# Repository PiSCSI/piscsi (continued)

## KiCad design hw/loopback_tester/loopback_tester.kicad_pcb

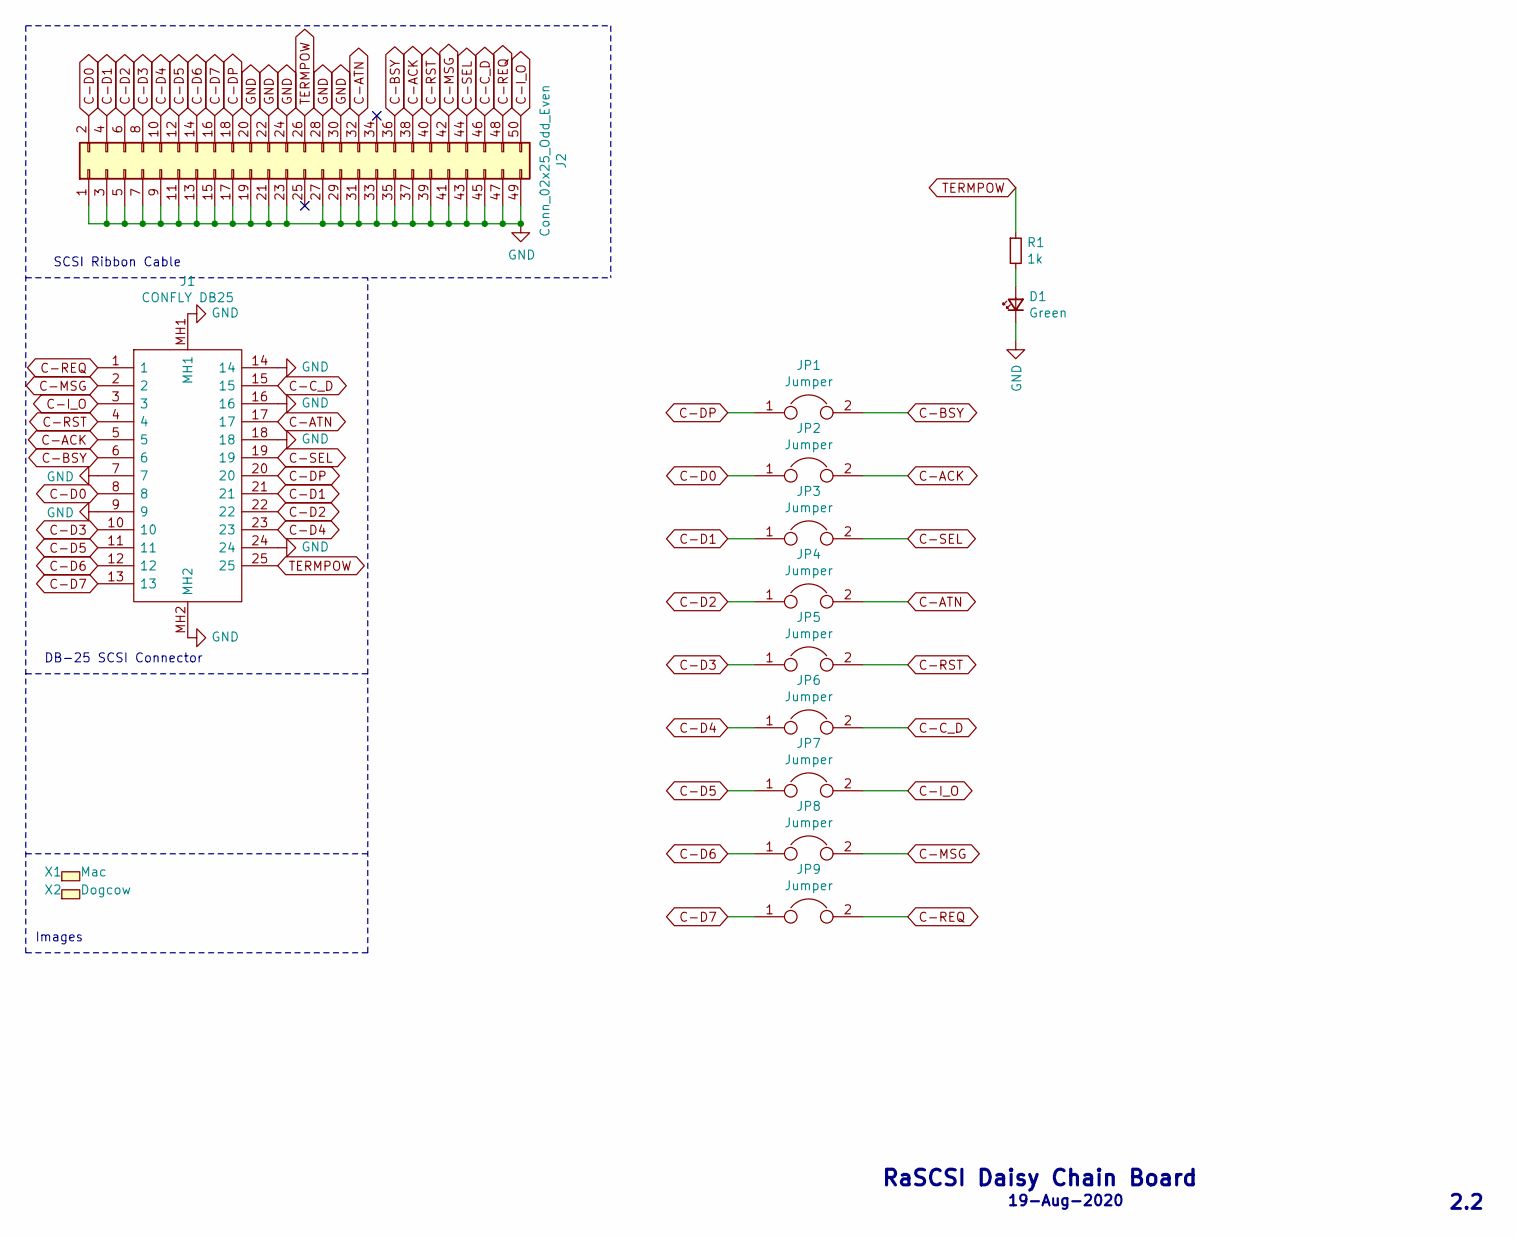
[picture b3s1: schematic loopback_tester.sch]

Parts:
D1: Green; LED_0805_2012Metric; LCSC C2297
J1: CONFLY DB25; L717SDB25PA4CH4F; Mouser Part Number 523-L717SDB25PA4CH4F
J2: Conn_02x25_Odd_Even; PinSocket_2x25_P2.54mm_Vertical; LCSC C40024
JP1, JP2, JP3, JP4, JP5, JP6, JP7, JP8, JP9: Jumper; SolderJumper-2_P1.3mm_Bridged_RoundedPad1.0x1.5mm
R1: 1k; R_0805_2012Metric; LCSC C17513
X1: Mac; mac_happy_small
X2: Dogcow; dogcow

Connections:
C-ACK: J1.5, J2.38, JP2.2
C-ATN: J1.17, J2.32, JP4.2
C-BSY: J1.6, J2.36, JP1.2
C-C_D: J1.15, J2.46, JP6.2
C-D0: J1.8, J2.2, JP2.1
C-D1: J1.21, J2.4, JP3.1
C-D2: J1.22, J2.6, JP4.1
C-D3: J1.10, J2.8, JP5.1
C-D4: J1.23, J2.10, JP6.1
C-D5: J1.11, J2.12, JP7.1
C-D6: J1.12, J2.14, JP8.1
C-D7: J1.13, J2.16, JP9.1
C-DP: J1.20, J2.18, JP1.1
C-I_O: J1.3, J2.50, JP7.2
C-MSG: J1.2, J2.42, JP8.2
C-REQ: J1.1, J2.48, JP9.2
C-RST: J1.4, J2.40, JP5.2
C-SEL: J1.19, J2.44, JP3.2
GND: D1.1 (K), J1.7, J1.9, J1.14, J1.16, J1.18, J1.24, J1.MH1, J1.MH2, J2.1, J2.3, J2.5, J2.7, J2.9, J2.11, J2.13, J2.15, J2.17, J2.19, J2.20, J2.21, J2.22, J2.23, J2.24, J2.27, J2.28, J2.29, J2.30, J2.31, J2.33, J2.35, J2.37, J2.39, J2.41, J2.43, J2.45, J2.47, J2.49
unnamed: D1.2 (A), R1.2
TERMPOW: J1.25, J2.26, R1.1

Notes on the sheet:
DB-25 SCSI Connector
SCSI Ribbon Cable
Images
RaSCSI Daisy Chain Board
2.2
19-Aug-2020

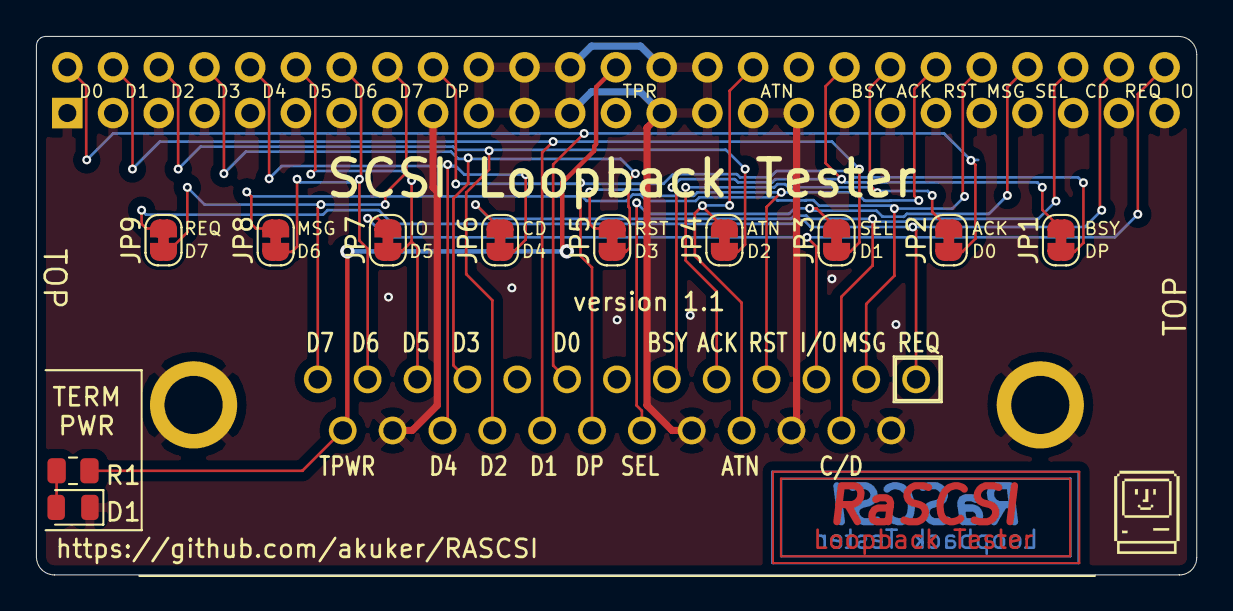
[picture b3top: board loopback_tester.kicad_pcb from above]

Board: 2 copper layers, 64.5 x 29.9 mm, 15 parts (0 on the bottom side), 21 nets.

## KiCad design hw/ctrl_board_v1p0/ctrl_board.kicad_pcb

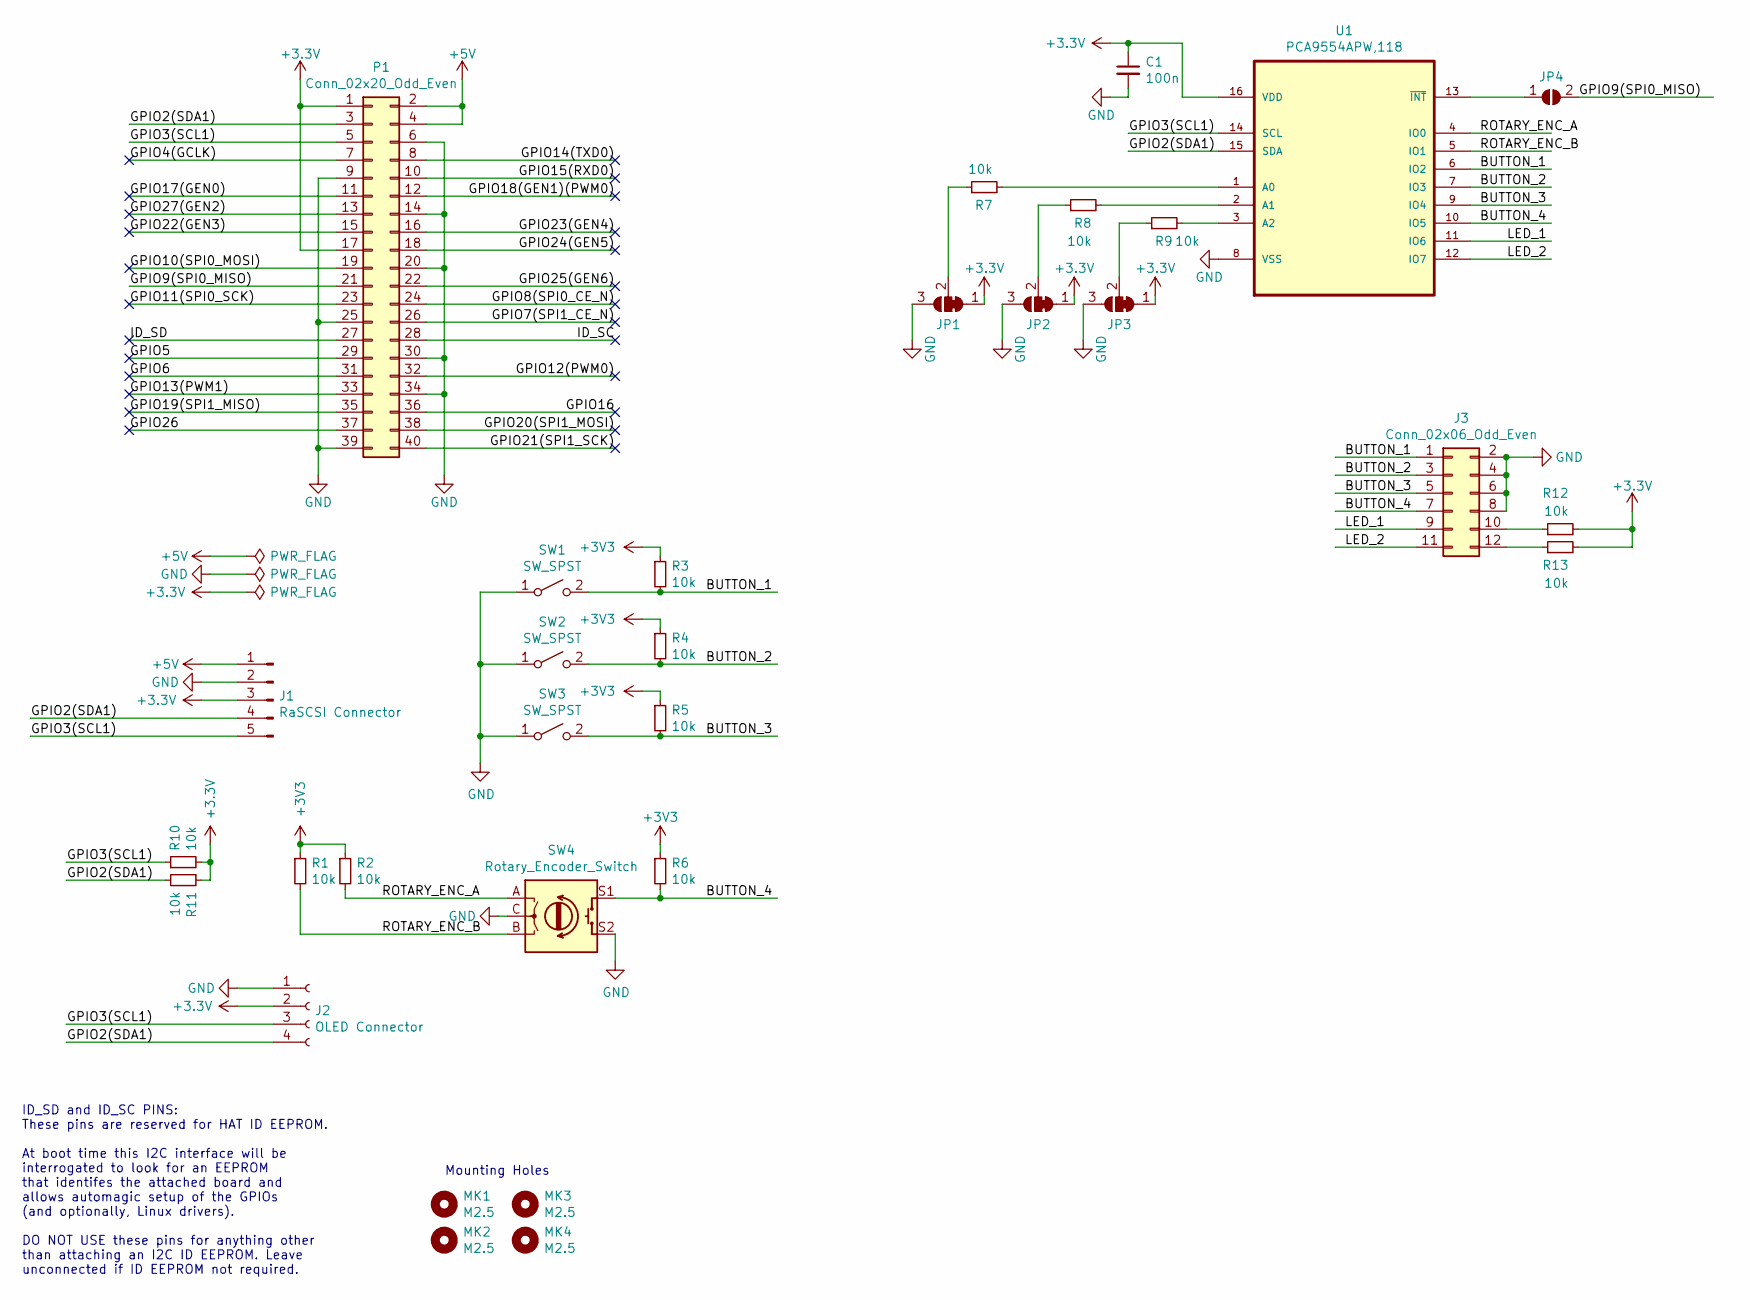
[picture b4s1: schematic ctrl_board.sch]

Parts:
C1: 100n; C_0805_2012Metric; LCSC C49678
J1: RaSCSI Connector; PinHeader_1x05_P2.54mm_Vertical
J2: OLED Connector; OLED_Footprint
J3: Conn_02x06_Odd_Even; PinHeader_2x06_P2.54mm_Vertical
JP1, JP2, JP3: SolderJumper_3_Bridged12; SolderJumper-3_P1.3mm_Bridged12_RoundedPad1.0x1.5mm
JP4: SolderJumper_2_Open; SolderJumper-2_P1.3mm_Open_RoundedPad1.0x1.5mm
MK1, MK2, MK3, MK4: M2.5; MountingHole_2.7mm_M2.5
P1: Conn_02x20_Odd_Even; PinSocket_2x20_P2.54mm_Vertical
R1, R2, R3, R4, R5, R6, R7, R8, R9, R10, R11, R12, R13: 10k; R_0805_2012Metric; LCSC C17414
SW1, SW2, SW3: SW_SPST; SW_PUSH_6mm_H5mm; LCSC C110153
SW4: Rotary_Encoder_Switch; RotaryEncoder_Alps_EC11E-Switch_Vertical_H20mm
U1: PCA9554APW,118; TSSOP-16_4.4x5mm_P0.65mm; MPN PCA9554APW,118

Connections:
+5V: J1.1, P1.2, P1.4
/BUTTON_1: J3.1, R3.2, SW1.2 (B), U1.6 (IO2)
/BUTTON_2: J3.3, R4.2, SW2.2 (B), U1.7 (IO3)
/BUTTON_3: J3.5, R5.2, SW3.2 (B), U1.9 (IO4)
/BUTTON_4: J3.7, R6.2, SW4.S1, U1.10 (IO5)
/GPIO2(SDA1): J1.4, J2.4, P1.3, R11.2, U1.15 (SDA)
/GPIO3(SCL1): J1.5, J2.3, P1.5, R10.1, U1.14 (SCL)
/GPIO4(GCLK): P1.7
/GPIO5: P1.29
/GPIO6: P1.31
/GPIO7(SPI1_CE_N): P1.26
/GPIO8(SPI0_CE_N): P1.24
/GPIO9(SPI0_MISO): JP4.2 (B), P1.21
/GPIO10(SPI0_MOSI): P1.19
/GPIO11(SPI0_SCK): P1.23
/GPIO12(PWM0): P1.32
/GPIO13(PWM1): P1.33
/GPIO14(TXD0): P1.8
/GPIO15(RXD0): P1.10
/GPIO16: P1.36
/GPIO17(GEN0): P1.11
/GPIO18(GEN1)(PWM0): P1.12
/GPIO19(SPI1_MISO): P1.35
/GPIO20(SPI1_MOSI): P1.38
/GPIO21(SPI1_SCK): P1.40
/GPIO22(GEN3): P1.15
/GPIO23(GEN4): P1.16
/GPIO24(GEN5): P1.18
/GPIO25(GEN6): P1.22
/GPIO26: P1.37
/GPIO27(GEN2): P1.13
/ID_SC: P1.28
/ID_SD: P1.27
/LED_1: J3.9, U1.11 (IO6)
/LED_2: J3.11, U1.12 (IO7)
/ROTARY_ENC_A: R2.2, SW4.A, U1.4 (IO0)
/ROTARY_ENC_B: R1.2, SW4.B, U1.5 (IO1)
GND: C1.2, J1.2, J2.1, J3.2, J3.4, J3.6, J3.8, JP1.3 (B), JP2.3 (B), JP3.3 (B), P1.6, P1.9, P1.14, P1.20, P1.25, P1.30, P1.34, P1.39, SW1.1 (A), SW2.1 (A), SW3.1 (A), SW4.C, SW4.S2, U1.8 (VSS)
unnamed: J3.10, R12.1
unnamed: J3.12, R13.1
unnamed: JP1.2 (C), R7.1
unnamed: JP2.2 (C), R8.1
unnamed: JP3.2 (C), R9.1
unnamed: JP4.1 (A), U1.13 (~INT)
unnamed: R7.2, U1.1 (A0)
unnamed: R8.2, U1.2 (A1)
unnamed: R9.2, U1.3 (A2)

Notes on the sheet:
ID_SD and ID_SC PINS: These pins are reserved for HAT ID EEPROM. At boot time this I2C interface will be interrogated to look for an EEPROM that identifes the attached board and allows automagic setup of the GPIOs (and optionally, Linux drivers). DO NOT USE these pins for anything other than attach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
Mounting Holes

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
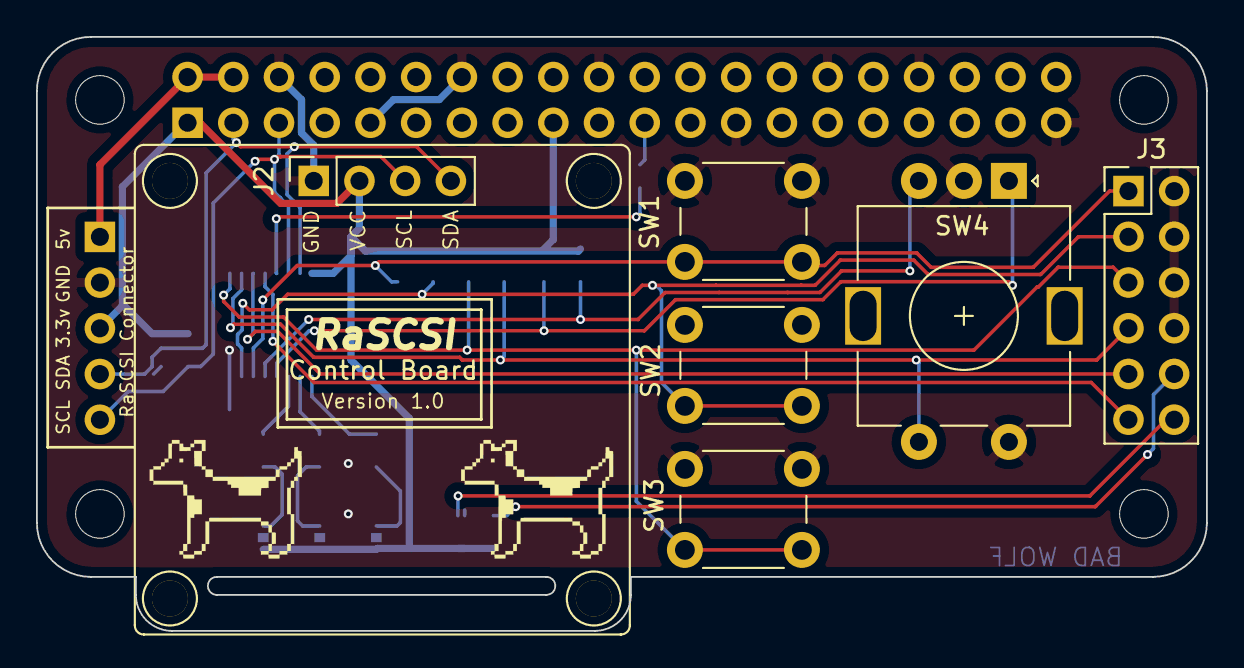
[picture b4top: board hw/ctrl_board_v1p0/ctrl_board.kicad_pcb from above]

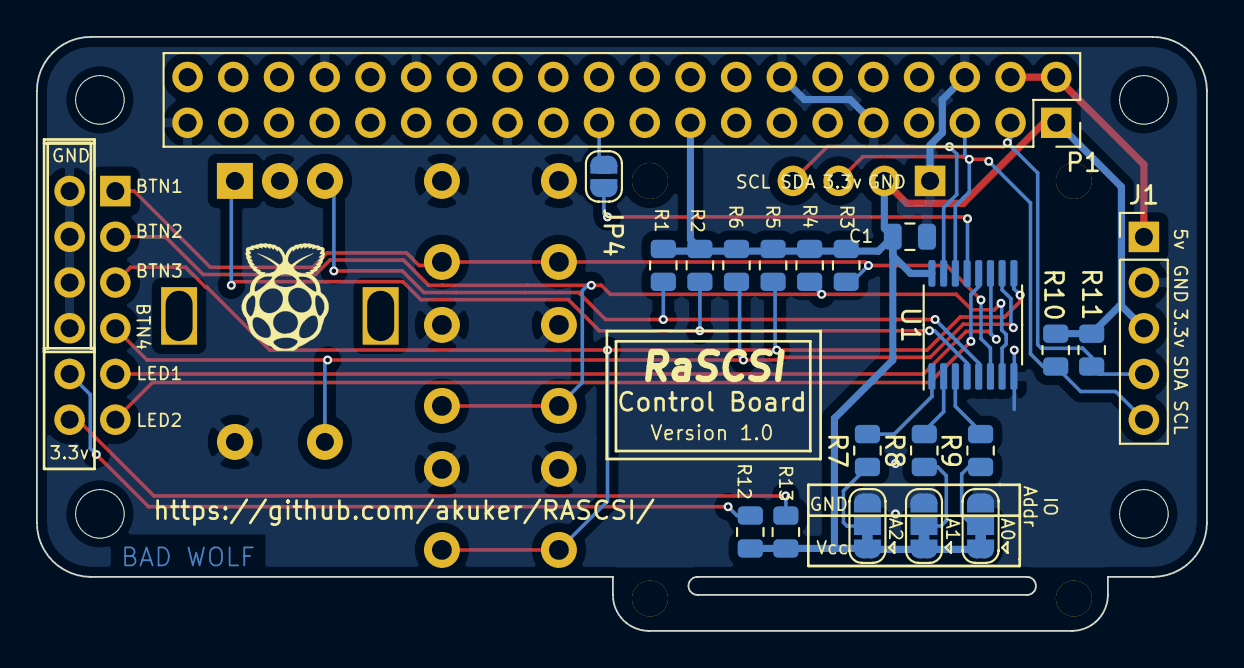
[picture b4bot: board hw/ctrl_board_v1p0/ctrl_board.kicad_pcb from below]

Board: 2 copper layers, 65.0 x 33.0 mm, 31 parts (21 on the bottom side), 23 nets.

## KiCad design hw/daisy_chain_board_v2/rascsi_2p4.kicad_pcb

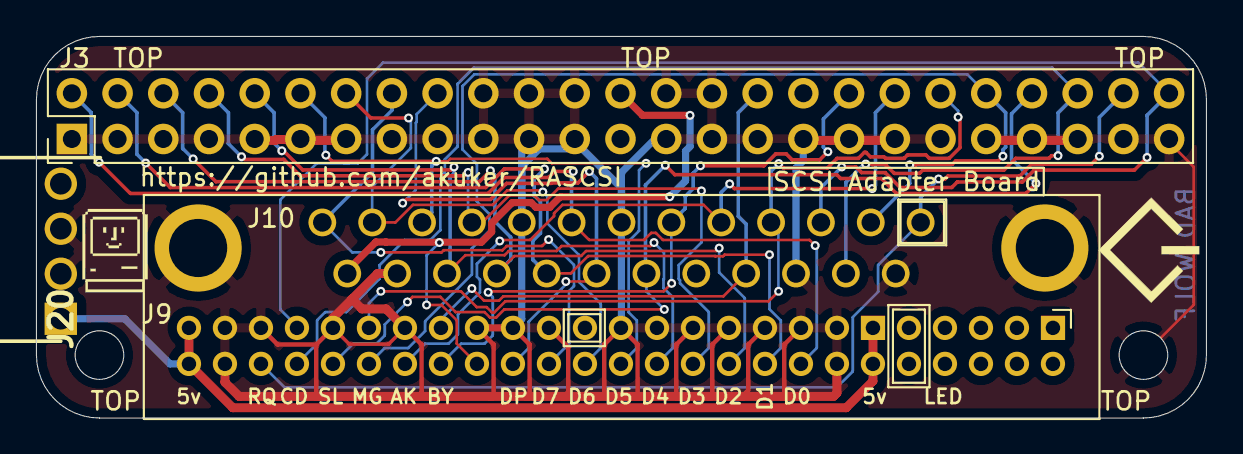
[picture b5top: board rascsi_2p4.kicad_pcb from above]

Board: 2 copper layers, 65.0 x 21.2 mm, 9 parts (0 on the bottom side), 21 nets.

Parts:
H5: Hole4; MountingHole_2.7mm_M2.5
H6: Hole6; MountingHole_2.7mm_M2.5
J3: Conn_02x25_Odd_Even; PinHeader_2x25_P2.54mm_Vertical
J6: CONNFLY DB-25; L717SDB25PA4CH4F
J9: Conn_02x25_Odd_Even; PinHeader_2x25_P2.00mm_Horizontal
J20: 171826-4; SHDRRA4W69P0X250_1X4_1000X1350X670P
X1, X3: Mac; mac_happy_small
X8: Pi; scsi_logo

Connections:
+5V: J9.11, J9.12, J9.49, J9.50, J20.1
C-ACK: J3.38, J6.5, J9.38
C-ATN: J3.32, J6.17, J9.35
C-BSY: J3.36, J6.6, J9.36
C-C_D: J3.46, J6.15, J9.44
C-D0: J3.2, J6.8, J9.16
C-D1: J3.4, J6.21, J9.18
C-D2: J3.6, J6.22, J9.20
C-D3: J3.8, J6.10, J9.22
C-D4: J3.10, J6.23, J9.24
C-D5: J3.12, J6.11, J9.26
C-D6: J3.14, J6.12, J9.28
C-D7: J3.16, J6.13, J9.30
C-DP: J3.18, J6.20, J9.32
C-I_O: J3.50, J6.3, J9.43
C-MSG: J3.42, J6.2, J9.40
C-REQ: J3.48, J6.1, J9.46
C-RST: J3.40, J6.4, J9.39
C-SEL: J3.44, J6.19, J9.42
GND: J3.1, J3.3, J3.5, J3.7, J3.9, J3.11, J3.13, J3.15, J3.17, J3.19, J3.20, J3.21, J3.22, J3.23, J3.24, J3.27, J3.28, J3.29, J3.30, J3.31, J3.33, J3.35, J3.37, J3.39, J3.41, J3.43, J3.45, J3.47, J3.49, J6.7, J6.9, J6.14, J6.16, J6.18, J6.24, J6.MH1, J6.MH2, J9.13, J9.14, J9.15, J9.17, J9.19, J9.21, J9.23, J9.25, J9.29, J9.31, J9.33, J9.37, J9.41, J9.45, J9.47, J9.48, J20.2, J20.3
TERMPOW: J3.26, J6.25, J9.34

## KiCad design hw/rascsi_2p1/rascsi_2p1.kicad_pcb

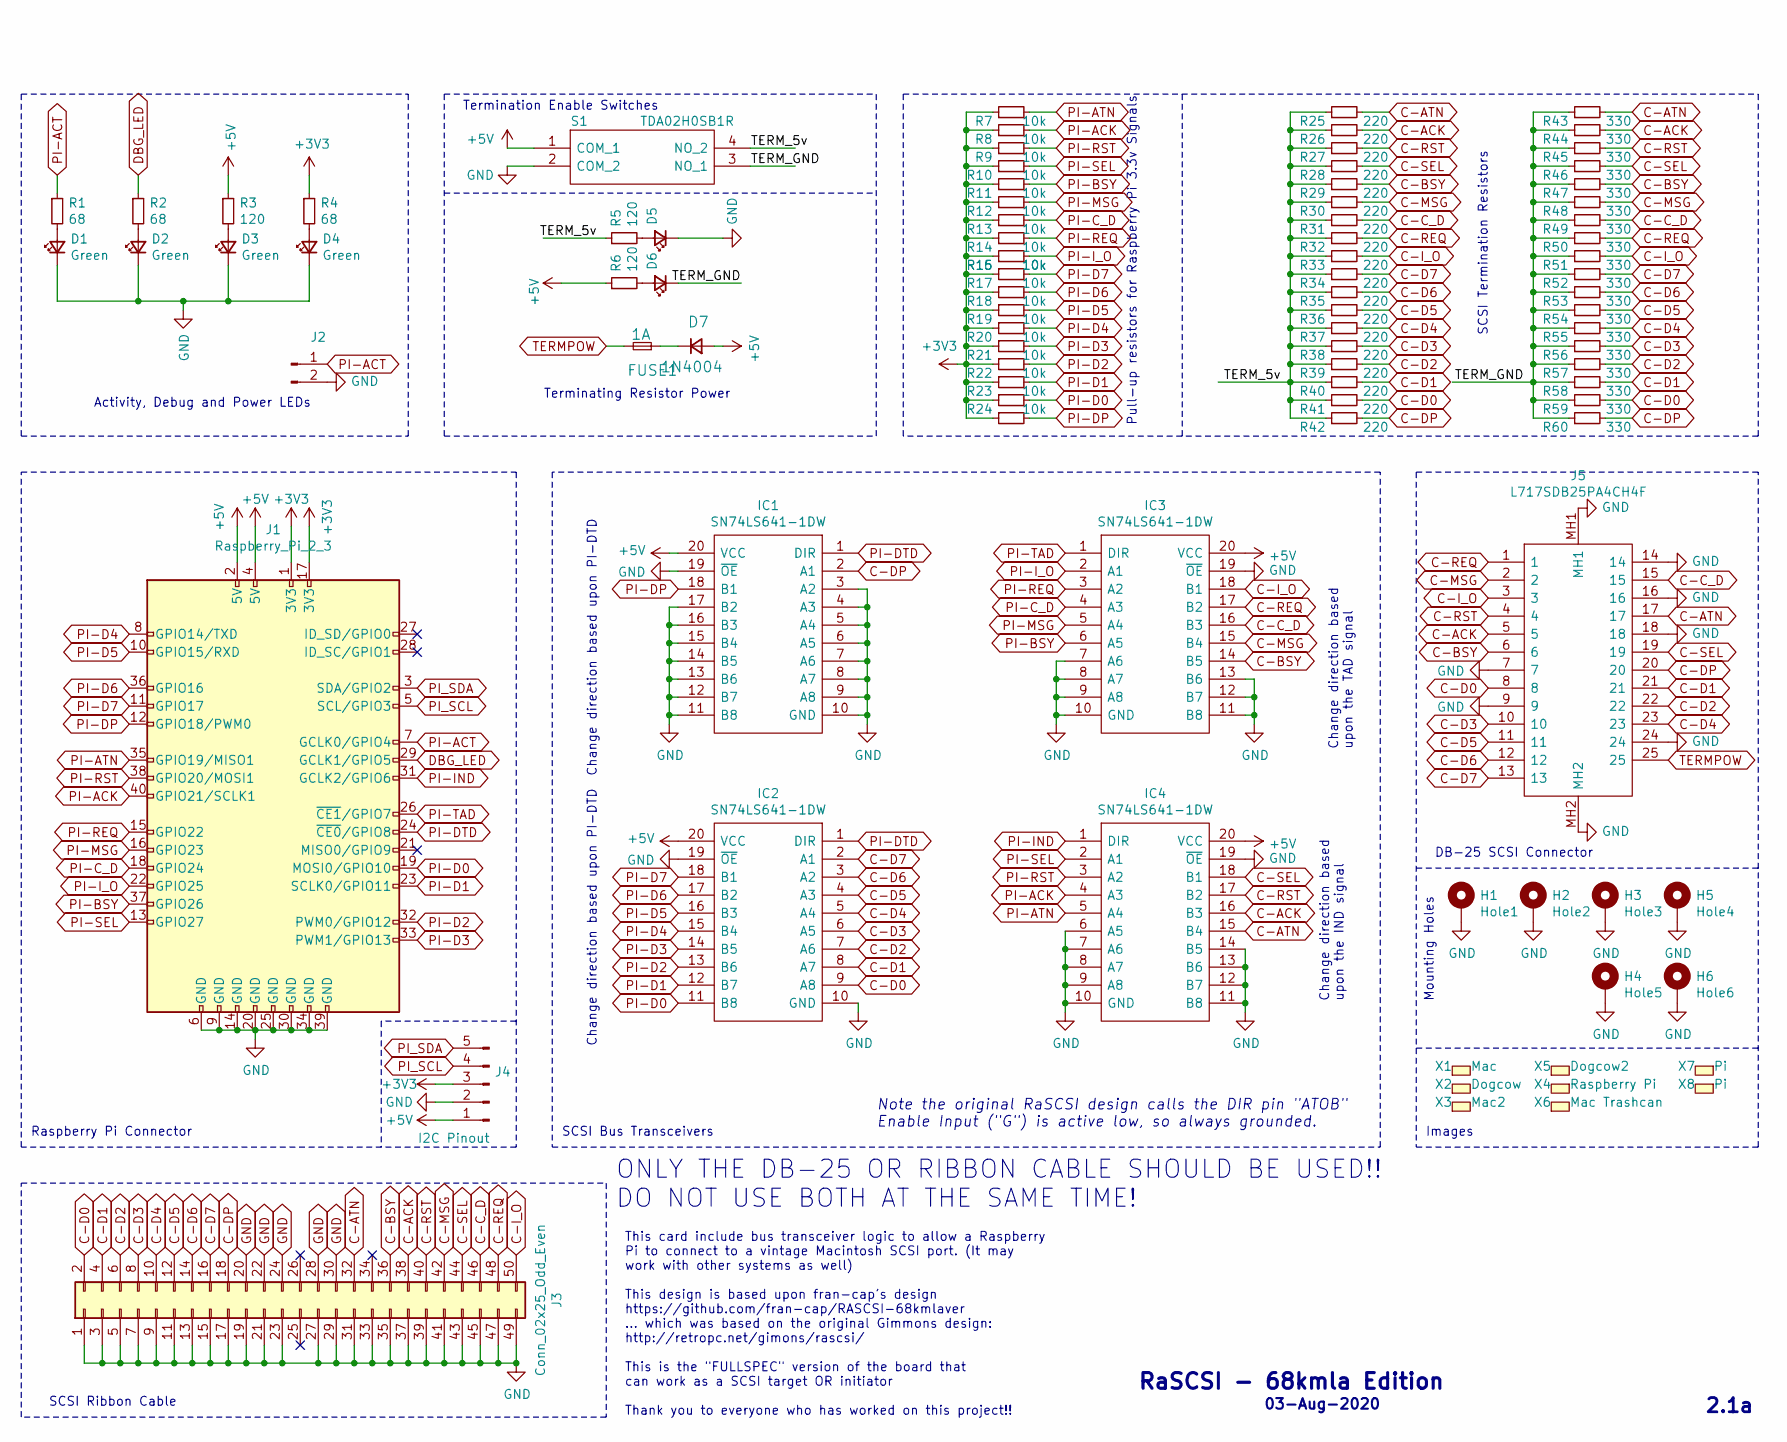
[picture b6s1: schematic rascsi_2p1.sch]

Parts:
D1, D2, D3, D4, D6: Green; LED_0805_2012Metric; LCSC C2297
D5: LED_Small; LED_0805_2012Metric; LCSC C2297
D7: 1N4004; D_SOD-123; LCSC C162734
FUSE1: 1A; Fuse_1206_3216Metric; LCSC C182974
H1: Hole1; MountingHole_2.7mm_M2.5_Pad_Via
H2: Hole2; MountingHole_2.7mm_M2.5_Pad_Via
H3: Hole3; MountingHole_2.7mm_M2.5_Pad_Via
H4: Hole5; MountingHole_2.7mm_M2.5_Pad_Via
H5: Hole4; MountingHole_2.7mm_M2.5_Pad_Via
H6: Hole6; MountingHole_2.7mm_M2.5_Pad_Via
IC1, IC2, IC3, IC4: SN74LS641-1DW; SOIC127P1030X265-20N; Manufacturer_Part_Number SN74LS641-1DW
J1: Raspberry_Pi_2_3; PinSocket_2x20_P2.54mm_Vertical
J2: Conn_01x02_Male; PinHeader_1x02_P2.54mm_Vertical
J3: Conn_02x25_Odd_Even; PinHeader_2x25_P2.54mm_Vertical
J4: I2C Pinout; PinSocket_1x05_P2.54mm_Vertical
J5: L717SDB25PA4CH4F; Mouser Part Number 523-L717SDB25PA4CH4F
R1, R2, R4: 68; R_0402_1005Metric; LCSC C36871
R3, R5, R6: 120; R_0402_1005Metric; LCSC C25079
R7, R8, R9, R10, R11, R12, R13, R14, R15, R16, R17, R18, R19, R20, R21, R22, R23, R24: 10k; R_0402_1005Metric; LCSC C25744
R25, R26, R27, R28, R29, R30, R31, R32, R33, R34, R35, R36, R37, R38, R39, R40, R41, R42: 220; R_0402_1005Metric; LCSC C25091
R43, R44, R45, R46, R47, R48, R49, R50, R51, R52, R53, R54, R55, R56, R57, R58, R59, R60: 330; R_0402_1005Metric; LCSC C25104
S1: TDA02H0SB1R; SOIC127P812X230-4N; Mouser Part Number 611-TDA02H0SB1R
X1: Mac; mac_happy_small
X2: Dogcow; dogcow
X3: Mac2; mac_happy_small
X4: Raspberry Pi; pi_logo
X5: Dogcow2; dogcow
X6: Mac Trashcan; mac_trashcan
X7: Pi; pi_logo
X8: Pi; scsi_logo

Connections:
+3V3: J1.1 (3V3), J1.17 (3V3), J4.3, R4.1, R7.1, R8.1, R9.1, R10.1, R11.1, R12.1, R13.1, R14.1, R15.1, R16.1, R17.1, R18.1, R19.1, R20.1, R21.1, R22.1, R23.1, R24.1
+5V: D7.2 (A), IC1.20 (VCC), IC2.20 (VCC), IC3.20 (VCC), IC4.20 (VCC), J1.2 (5V), J1.4 (5V), J4.1, R3.1, R6.1, S1.1 (COM_1)
/TERM_5v: R5.1, R25.1, R26.1, R27.1, R28.1, R29.1, R30.1, R31.1, R32.1, R33.1, R34.1, R35.1, R36.1, R37.1, R38.1, R39.1, R40.1, R41.1, R42.1, S1.4 (NO_2)
/TERM_GND: D6.1 (K), R43.1, R44.1, R45.1, R46.1, R47.1, R48.1, R49.1, R50.1, R51.1, R52.1, R53.1, R54.1, R55.1, R56.1, R57.1, R58.1, R59.1, R60.1, S1.3 (NO_1)
C-ACK: IC4.16 (B3), J3.38, J5.5, R26.2, R44.2
C-ATN: IC4.15 (B4), J3.32, J5.17, R25.2, R43.2
C-BSY: IC3.14 (B5), J3.36, J5.6, R29.2, R47.2
C-C_D: IC3.16 (B3), J3.46, J5.15, R31.2, R49.2
C-D0: IC2.9 (A8), J3.2, J5.8, R41.2, R59.2
C-D1: IC2.8 (A7), J3.4, J5.21, R40.2, R58.2
C-D2: IC2.7 (A6), J3.6, J5.22, R39.2, R57.2
C-D3: IC2.6 (A5), J3.8, J5.10, R38.2, R56.2
C-D4: IC2.5 (A4), J3.10, J5.23, R37.2, R55.2
C-D5: IC2.4 (A3), J3.12, J5.11, R36.2, R54.2
C-D6: IC2.3 (A2), J3.14, J5.12, R35.2, R53.2
C-D7: IC2.2 (A1), J3.16, J5.13, R34.2, R52.2
C-DP: IC1.2 (A1), J3.18, J5.20, R42.2, R60.2
C-I_O: IC3.18 (B1), J3.50, J5.3, R33.2, R51.2
C-MSG: IC3.15 (B4), J3.42, J5.2, R30.2, R48.2
C-REQ: IC3.17 (B2), J3.48, J5.1, R32.2, R50.2
C-RST: IC4.17 (B2), J3.40, J5.4, R27.2, R45.2
C-SEL: IC4.18 (B1), J3.44, J5.19, R28.2, R46.2
DBG_LED: J1.29 (GCLK1/GPIO5), R2.1
GND: D1.1 (K), D2.1 (K), D3.1 (K), D4.1 (K), D5.1 (K), H1.1, H2.1, H3.1, H4.1, H5.1, H6.1, IC1.3 (A2), IC1.4 (A3), IC1.5 (A4), IC1.6 (A5), IC1.7 (A6), IC1.8 (A7), IC1.9 (A8), IC1.10 (GND), IC1.11 (B8), IC1.12 (B7), IC1.13 (B6), IC1.14 (B5), IC1.15 (B4), IC1.16 (B3), IC1.17 (B2), IC1.19 (~OE), IC2.10 (GND), IC2.19 (~OE), IC3.7 (A6), IC3.8 (A7), IC3.9 (A8), IC3.10 (GND), IC3.11 (B8), IC3.12 (B7), IC3.13 (B6), IC3.19 (~OE), IC4.6 (A5), IC4.7 (A6), IC4.8 (A7), IC4.9 (A8), IC4.10 (GND), IC4.11 (B8), IC4.12 (B7), IC4.13 (B6), IC4.14 (B5), IC4.19 (~OE), J1.6 (GND), J1.9 (GND), J1.14 (GND), J1.20 (GND), J1.25 (GND), J1.30 (GND), J1.34 (GND), J1.39 (GND), J2.2, J3.1, J3.3, J3.5, J3.7, J3.9, J3.11, J3.13, J3.15, J3.17, J3.19, J3.20, J3.21, J3.22, J3.23, J3.24, J3.27, J3.28, J3.29, J3.30, J3.31, J3.33, J3.35, J3.37, J3.39, J3.41, J3.43, J3.45, J3.47, J3.49, J4.2, J5.7, J5.9, J5.14, J5.16, J5.18, J5.24, J5.MH1, J5.MH2, S1.2 (COM_2)
unnamed: D1.2 (A), R1.2
unnamed: D2.2 (A), R2.2
unnamed: D3.2 (A), R3.2
unnamed: D4.2 (A), R4.2
unnamed: D5.2 (A), R5.2
unnamed: D6.2 (A), R6.2
unnamed: D7.1 (K), FUSE1.1
PI-ACK: IC4.4 (A3), J1.40 (GPIO21/SCLK1), R8.2
PI-ACT: J1.7 (GCLK0/GPIO4), J2.1, R1.1
PI-ATN: IC4.5 (A4), J1.35 (GPIO19/MISO1), R7.2
PI-BSY: IC3.6 (A5), J1.37 (GPIO26), R11.2
PI-C_D: IC3.4 (A3), J1.18 (GPIO24), R13.2
PI-D0: IC2.11 (B8), J1.19 (MOSI0/GPIO10), R23.2
PI-D1: IC2.12 (B7), J1.23 (SCLK0/GPIO11), R22.2
PI-D2: IC2.13 (B6), J1.32 (PWM0/GPIO12), R21.2
PI-D3: IC2.14 (B5), J1.33 (PWM1/GPIO13), R20.2
PI-D4: IC2.15 (B4), J1.8 (GPIO14/TXD), R19.2
PI-D5: IC2.16 (B3), J1.10 (GPIO15/RXD), R18.2
PI-D6: IC2.17 (B2), J1.36 (GPIO16), R17.2
PI-D7: IC2.18 (B1), J1.11 (GPIO17), R16.2
PI-DP: IC1.18 (B1), J1.12 (GPIO18/PWM0), R24.2
PI-DTD: IC1.1 (DIR), IC2.1 (DIR), J1.24 (~CE0~/GPIO8)
PI-IND: IC4.1 (DIR), J1.31 (GCLK2/GPIO6)
PI-I_O: IC3.2 (A1), J1.22 (GPIO25), R15.2
PI-MSG: IC3.5 (A4), J1.16 (GPIO23), R12.2
PI-REQ: IC3.3 (A2), J1.15 (GPIO22), R14.2
PI-RST: IC4.3 (A2), J1.38 (GPIO20/MOSI1), R9.2
PI-SEL: IC4.2 (A1), J1.13 (GPIO27), R10.2
PI-TAD: IC3.1 (DIR), J1.26 (~CE1~/GPIO7)
PI_SCL: J1.5 (SCL/GPIO3), J4.4
PI_SDA: J1.3 (SDA/GPIO2), J4.5
TERMPOW: FUSE1.2, J5.25

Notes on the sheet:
Note the original RaSCSI design calls the DIR pin "ATOB" Enable Input ("G") is active low, so always grounded.
Activity, Debug and Power LEDs
Pull-up resistors for Raspberry Pi 3.3v Signals
Raspberry Pi Connector
Terminating Resistor Power
SCSI Bus Transceivers
Change direction based upon PI-DTD
Change direction based upon the IND signal
Change direction based upon the TAD signal
DB-25 SCSI Connector
SCSI Ribbon Cable
ONLY THE DB-25 OR RIBBON CABLE SHOULD BE USED!! DO NOT USE BOTH AT THE SAME TIME!
This card include bus transceiver logic to allow a Raspberry Pi to connect to a vintage Macintosh SCSI port. (It may work with other systems as well) This design is based upon fran-cap's design https://github.com/fran-cap/RASCSI-68kmlaver ... which was based on the original Gimmons design: http://r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
Images
Mounting Holes
Termination Enable Switches
SCSI Termination Resistors
RaSCSI - 68kmla Edition
2.1a
03-Aug-2020

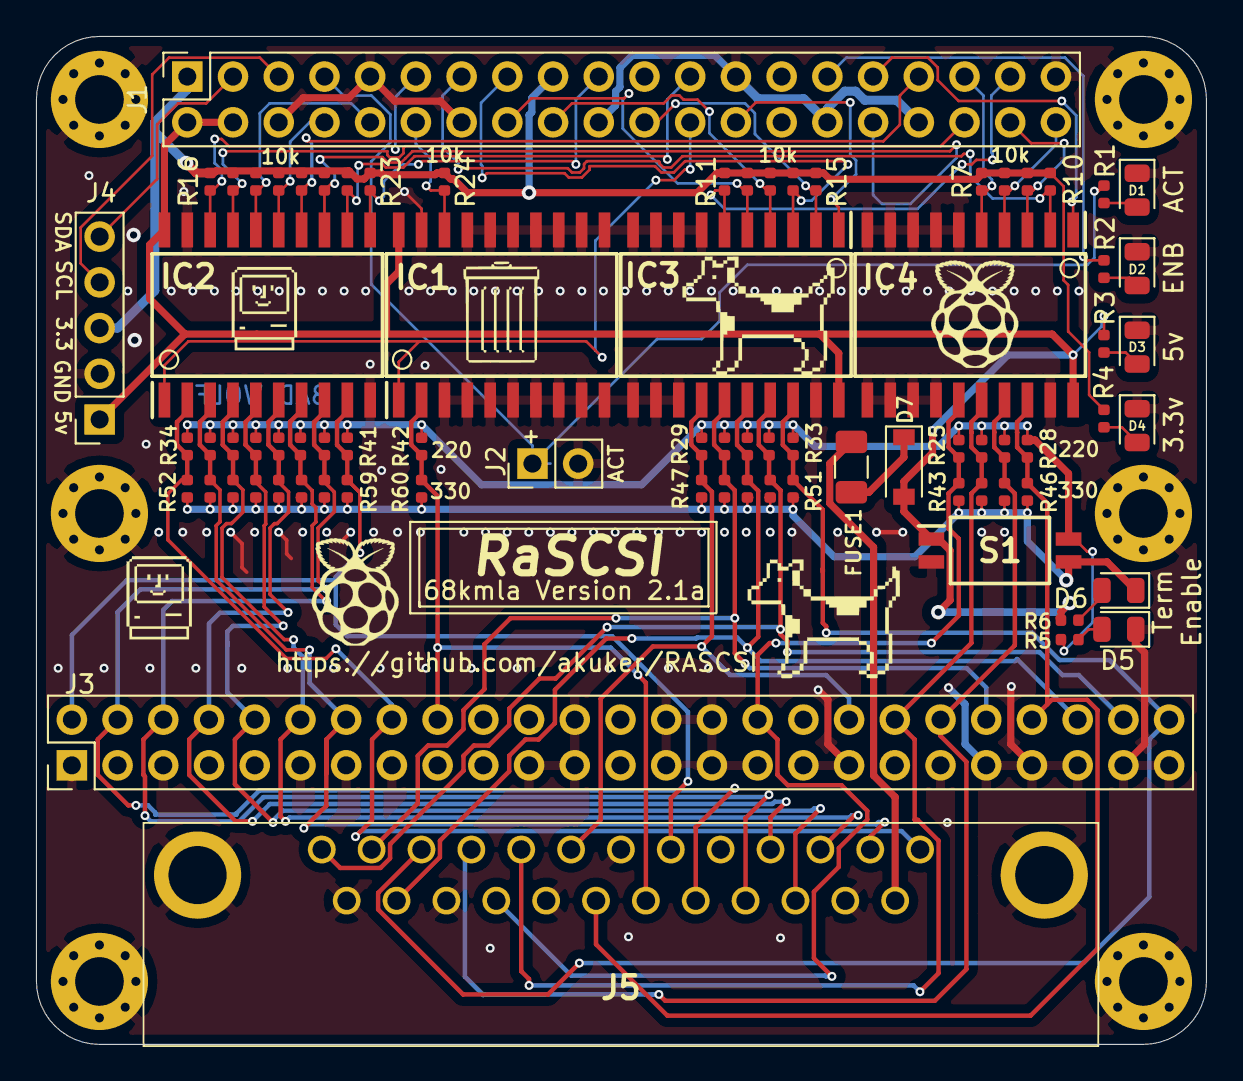
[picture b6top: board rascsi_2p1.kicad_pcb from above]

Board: 2 copper layers, 65.0 x 56.0 mm, 91 parts (0 on the bottom side), 56 nets.

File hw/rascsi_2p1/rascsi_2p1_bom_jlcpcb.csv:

Comment,Designator,Footprint,LCSC
"Green","D1,D2,D3,D4,D6","LED_SMD:LED_0805_2012Metric","C2297"
"LED_Small","D5","LED_SMD:LED_0805_2012Metric","C2297"
"1N4004","D7","Diode_SMD:D_SOD-123","C162734"
"1A","FUSE1","Fuse:Fuse_1206_3216Metric","C182974"
"Hole1","H1","MountingHole:MountingHole_2.7mm_M2.5_Pad_Via",""
"Hole2","H2","MountingHole:MountingHole_2.7mm_M2.5_Pad_Via",""
"Hole3","H3","MountingHole:MountingHole_2.7mm_M2.5_Pad_Via",""
"Hole5","H4","MountingHole:MountingHole_2.7mm_M2.5_Pad_Via",""
"Hole4","H5","MountingHole:MountingHole_2.7mm_M2.5_Pad_Via",""
"Hole6","H6","MountingHole:MountingHole_2.7mm_M2.5_Pad_Via",""
"SN74LS245DW","IC1,IC2,IC3,IC4","SOIC127P1030X265-20N","C129580"
"Raspberry_Pi_2_3","J1","Connector_PinSocket_2.54mm:PinSocket_2x20_P2.54mm_Vertical",""
"Conn_01x02_Male","J2","Connector_PinHeader_2.54mm:PinHeader_1x02_P2.54mm_Vertical",""
"Conn_02x25_Odd_Even","J3","Connector_PinHeader_2.54mm:PinHeader_2x25_P2.54mm_Vertical",""
"I2C Pinout","J4","Connector_PinSocket_2.54mm:PinSocket_1x05_P2.54mm_Vertical",""
"L717SDB25PA4CH4F","J5","L717SDB25PA4CH4F",""
"68","R1,R2,R4","Resistor_SMD:R_0402_1005Metric","C36871"
"10k","R7,R8,R9,R10,R11,R12,R13,R14,R15,R16,R17,R18,R19,R20,R21,R22,R23,R24","Resistor_SMD:R_0402_1005Metric","C25744"
"220","R25,R26,R27,R28,R29,R30,R31,R32,R33,R34,R35,R36,R37,R38,R39,R40,R41,R42","Resistor_SMD:R_0402_1005Metric","C25091"
"330","R43,R44,R45,R46,R47,R48,R49,R50,R51,R52,R53,R54,R55,R56,R57,R58,R59,R60","Resistor_SMD:R_0402_1005Metric","C25104"
"120","R3,R5,R6","Resistor_SMD:R_0402_1005Metric","C25079"
"TDA02H0SB1R","S1","rascsi_din:SOIC127P812X230-4N",""
"Mac","X1","SamacSys_Parts:mac_happy_small",""
"Dogcow","X2","SamacSys_Parts:dogcow",""
"Mac2","X3","SamacSys_Parts:mac_happy_small",""
"Raspberry Pi","X4","SamacSys_Parts:pi_logo",""
"Dogcow2","X5","SamacSys_Parts:dogcow",""
"Mac Trashcan","X6","SamacSys_Parts:mac_trashcan",""
"Pi","X7","SamacSys_Parts:pi_logo",""
"Pi","X8","SamacSys_Parts:scsi_logo",""

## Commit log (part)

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2025-12-29 Bump luma-core from 2.4.1 to 2.5.3 in /python
    Bumps [luma-core](https://github.com/rm-hull/luma.core) from 2.4.1 to 2.5.3.
    - [Changelog](https://github.com/rm-hull/luma.core/blob/main/CHANGES.rst)
    - [Commits](https://github.com/rm-hull/luma.core/compare/2.4.1...2.5.3)
    ---
    updated-dependencies:
    - dependency-name: luma-core
2025-12-29 Bump charset-normalizer from 2.1.1 to 3.4.4 in /python
    Bumps [charset-normalizer](https://github.com/jawah/charset_normalizer) from 2.1.1 to 3.4.4.
    - [Release notes](https://github.com/jawah/charset_normalizer/releases)
    - [Changelog](https://github.com/jawah/charset_normalizer/blob/master/CHANGELOG.md)
    - [Commits](https://github.com/jawah/charset_normalizer/compare/2.1.1...3.4.4)
    ---
    updated-dependencies:
2025-12-30 Downgrade Adafruit-Blinka version to 8.50.0
    Adafruit-Blinka 8.50.0 is the final version of this package that works with python 3.9
    8.51.0 and later introduced a dependency on the Adafruit-Blinka-Raspberry-Pi5-Neopixel package which requires python 3.11
2025-12-31 improve mdoc syntax in man pages
    Use proper idiomatic mdoc syntax, notably removing any empty lines or trailing white spaces
    Explicitly set a project name to suppress the default OS label
2026-01-01 fixes
2026-01-05 Bump pyftdi from 0.55.0 to 0.57.1 in /python
    Bumps [pyftdi](https://github.com/eblot/pyftdi) from 0.55.0 to 0.57.1.
    - [Release notes](https://github.com/eblot/pyftdi/releases)
    - [Commits](https://github.com/eblot/pyftdi/compare/v0.55.0...v0.57.1)
    ---
    updated-dependencies:
    - dependency-name: pyftdi
2026-01-05 Bump certifi from 2025.11.12 to 2026.1.4 in /python
    Bumps [certifi](https://github.com/certifi/python-certifi) from 2025.11.12 to 2026.1.4.
    - [Commits](https://github.com/certifi/python-certifi/compare/2025.11.12...2026.01.04)
    ---
    updated-dependencies:
    - dependency-name: certifi
    dependency-version: 2026.1.4
2026-01-09 Bump werkzeug from 3.1.4 to 3.1.5 in /python/web
    Bumps [werkzeug](https://github.com/pallets/werkzeug) from 3.1.4 to 3.1.5.
    - [Release notes](https://github.com/pallets/werkzeug/releases)
    - [Changelog](https://github.com/pallets/werkzeug/blob/main/CHANGES.rst)
    - [Commits](https://github.com/pallets/werkzeug/compare/3.1.4...3.1.5)
    ---
    updated-dependencies:
2026-01-12 Bump tomli from 2.3.0 to 2.4.0 in /python
    Bumps [tomli](https://github.com/hukkin/tomli) from 2.3.0 to 2.4.0.
    - [Changelog](https://github.com/hukkin/tomli/blob/master/CHANGELOG.md)
    - [Commits](https://github.com/hukkin/tomli/compare/2.3.0...2.4.0)
    ---
    updated-dependencies:
    - dependency-name: tomli
2026-01-12 WIPMacPlus
2026-01-13 test read6
2026-01-19 Bump stylelint from 16.26.1 to 17.0.0 in /python/web
    Bumps [stylelint](https://github.com/stylelint/stylelint) from 16.26.1 to 17.0.0.
    - [Release notes](https://github.com/stylelint/stylelint/releases)
    - [Changelog](https://github.com/stylelint/stylelint/blob/main/CHANGELOG.md)
    - [Commits](https://github.com/stylelint/stylelint/compare/16.26.1...17.0.0)
    ---
    updated-dependencies:
2026-01-19 Bump actions/setup-node from 6.1.0 to 6.2.0 in /.github/workflows
    Bumps [actions/setup-node](https://github.com/actions/setup-node) from 6.1.0 to 6.2.0.
    - [Release notes](https://github.com/actions/setup-node/releases)
    - [Commits](https://github.com/actions/setup-node/compare/395ad3262231945c25e8478fd5baf05154b1d79f...6044e13b5dc448c55e2357c09f80417699197238)
    ---
    updated-dependencies:
    - dependency-name: actions/setup-node
2026-02-02 Bump stylelint from 16.26.1 to 17.1.0 in /python/web
    Bumps [stylelint](https://github.com/stylelint/stylelint) from 16.26.1 to 17.1.0.
    - [Release notes](https://github.com/stylelint/stylelint/releases)
    - [Changelog](https://github.com/stylelint/stylelint/blob/main/CHANGELOG.md)
    - [Commits](https://github.com/stylelint/stylelint/compare/16.26.1...17.1.0)
    ---
    updated-dependencies:
2026-02-11 Bump pillow from 11.3.0 to 12.1.1 in /python/ctrlboard
    Bumps [pillow](https://github.com/python-pillow/Pillow) from 11.3.0 to 12.1.1.
    - [Release notes](https://github.com/python-pillow/Pillow/releases)
    - [Changelog](https://github.com/python-pillow/Pillow/blob/main/CHANGES.rst)
    - [Commits](https://github.com/python-pillow/Pillow/compare/11.3.0...12.1.1)
    ---
    updated-dependencies:
2026-02-11 Bump actions/checkout from 6.0.1 to 6.0.2 in /.github/workflows
    Bumps [actions/checkout](https://github.com/actions/checkout) from 6.0.1 to 6.0.2.
    - [Release notes](https://github.com/actions/checkout/releases)
    - [Changelog](https://github.com/actions/checkout/blob/main/CHANGELOG.md)
    - [Commits](https://github.com/actions/checkout/compare/8e8c483db84b4bee98b60c0593521ed34d9990e8...de0fac2e4500dabe0009e67214ff5f5447ce83dd)
    ---
    updated-dependencies:
2026-02-16 Bump packaging from 25.0 to 26.0 in /python
    Bumps [packaging](https://github.com/pypa/packaging) from 25.0 to 26.0.
    - [Release notes](https://github.com/pypa/packaging/releases)
    - [Changelog](https://github.com/pypa/packaging/blob/main/CHANGELOG.rst)
    - [Commits](https://github.com/pypa/packaging/compare/25.0...26.0)
    ---
    updated-dependencies:
2026-02-16 Bump pytest-httpserver from 1.1.3 to 1.1.5 in /python
    Bumps [pytest-httpserver](https://github.com/csernazs/pytest-httpserver) from 1.1.3 to 1.1.5.
    - [Release notes](https://github.com/csernazs/pytest-httpserver/releases)
    - [Changelog](https://github.com/csernazs/pytest-httpserver/blob/master/CHANGES.rst)
    - [Commits](https://github.com/csernazs/pytest-httpserver/compare/1.1.3...1.1.5)
    ---
    updated-dependencies:
2026-02-23 Bump werkzeug from 3.1.5 to 3.1.6 in /python
    Bumps [werkzeug](https://github.com/pallets/werkzeug) from 3.1.5 to 3.1.6.
    - [Release notes](https://github.com/pallets/werkzeug/releases)
    - [Changelog](https://github.com/pallets/werkzeug/blob/main/CHANGES.rst)
    - [Commits](https://github.com/pallets/werkzeug/compare/3.1.5...3.1.6)
    ---
    updated-dependencies:
2026-03-02 Bump adafruit-platformdetect from 3.87.0 to 3.88.0 in /python
    Bumps [adafruit-platformdetect](https://github.com/adafruit/Adafruit_Python_PlatformDetect) from 3.87.0 to 3.88.0.
    - [Release notes](https://github.com/adafruit/Adafruit_Python_PlatformDetect/releases)
    - [Commits](https://github.com/adafruit/Adafruit_Python_PlatformDetect/compare/3.87.0...3.88.0)
    ---
    updated-dependencies:
    - dependency-name: adafruit-platformdetect
2026-03-09 Bump actions/setup-node from 6.2.0 to 6.3.0 in /.github/workflows
    Bumps [actions/setup-node](https://github.com/actions/setup-node) from 6.2.0 to 6.3.0.
    - [Release notes](https://github.com/actions/setup-node/releases)
    - [Commits](https://github.com/actions/setup-node/compare/6044e13b5dc448c55e2357c09f80417699197238...53b83947a5a98c8d113130e565377fae1a50d02f)
    ---
    updated-dependencies:
    - dependency-name: actions/setup-node
2026-03-09 Bump charset-normalizer from 3.4.4 to 3.4.5 in /python
    Bumps [charset-normalizer](https://github.com/jawah/charset_normalizer) from 3.4.4 to 3.4.5.
    - [Release notes](https://github.com/jawah/charset_normalizer/releases)
    - [Changelog](https://github.com/jawah/charset_normalizer/blob/master/CHANGELOG.md)
    - [Commits](https://github.com/jawah/charset_normalizer/compare/3.4.4...3.4.5)
    ---
    updated-dependencies:
2026-03-16 Bump charset-normalizer from 3.4.4 to 3.4.6 in /python
    Bumps [charset-normalizer](https://github.com/jawah/charset_normalizer) from 3.4.4 to 3.4.6.
    - [Release notes](https://github.com/jawah/charset_normalizer/releases)
    - [Changelog](https://github.com/jawah/charset_normalizer/blob/master/CHANGELOG.md)
    - [Commits](https://github.com/jawah/charset_normalizer/compare/3.4.4...3.4.6)
    ---
    updated-dependencies:
2026-03-26 Bump picomatch from 2.3.1 to 2.3.2 in /python/web
    Bumps [picomatch](https://github.com/micromatch/picomatch) from 2.3.1 to 2.3.2.
    - [Release notes](https://github.com/micromatch/picomatch/releases)
    - [Changelog](https://github.com/micromatch/picomatch/blob/master/CHANGELOG.md)
    - [Commits](https://github.com/micromatch/picomatch/compare/2.3.1...2.3.2)
    ---
    updated-dependencies:
2026-03-26 revert to markupsafe v2.1.5 for backwards compatibility
2026-03-30 Bump adafruit-circuitpython-connectionmanager in /python
    Bumps [adafruit-circuitpython-connectionmanager](https://github.com/adafruit/Adafruit_CircuitPython_ConnectionManager) from 3.1.6 to 3.1.7.
    - [Release notes](https://github.com/adafruit/Adafruit_CircuitPython_ConnectionManager/releases)
    - [Commits](https://github.com/adafruit/Adafruit_CircuitPython_ConnectionManager/compare/3.1.6...3.1.7)
    ---
    updated-dependencies:
    - dependency-name: adafruit-circuitpython-connectionmanager
2026-03-30 Bump requests from 2.32.5 to 2.33.0 in /python
    Bumps [requests](https://github.com/psf/requests) from 2.32.5 to 2.33.0.
    - [Release notes](https://github.com/psf/requests/releases)
    - [Changelog](https://github.com/psf/requests/blob/main/HISTORY.md)
    - [Commits](https://github.com/psf/requests/compare/v2.32.5...v2.33.0)
    ---
    updated-dependencies:
2026-04-06 Bump docker/login-action from 4.0.0 to 4.1.0 in /.github/workflows
    Bumps [docker/login-action](https://github.com/docker/login-action) from 4.0.0 to 4.1.0.
    - [Release notes](https://github.com/docker/login-action/releases)
    - [Commits](https://github.com/docker/login-action/compare/b45d80f862d83dbcd57f89517bcf500b2ab88fb2...4907a6ddec9925e35a0a9e82d7399ccc52663121)
    ---
    updated-dependencies:
    - dependency-name: docker/login-action
2026-04-13 Bump actions/upload-artifact from 7.0.0 to 7.0.1 in /.github/workflows
    Bumps [actions/upload-artifact](https://github.com/actions/upload-artifact) from 7.0.0 to 7.0.1.
    - [Release notes](https://github.com/actions/upload-artifact/releases)
    - [Commits](https://github.com/actions/upload-artifact/compare/bbbca2ddaa5d8feaa63e36b76fdaad77386f024f...043fb46d1a93c77aae656e7c1c64a875d1fc6a0a)
    ---
    updated-dependencies:
    - dependency-name: actions/upload-artifact
2026-04-20 Bump actions/setup-node from 6.3.0 to 6.4.0 in /.github/workflows
    Bumps [actions/setup-node](https://github.com/actions/setup-node) from 6.3.0 to 6.4.0.
    - [Release notes](https://github.com/actions/setup-node/releases)
    - [Commits](https://github.com/actions/setup-node/compare/53b83947a5a98c8d113130e565377fae1a50d02f...48b55a011bda9f5d6aeb4c2d9c7362e8dae4041e)
    ---
    updated-dependencies:
    - dependency-name: actions/setup-node
2026-05-09 Bump postcss from 8.5.6 to 8.5.14 in /python/web
    Bumps [postcss](https://github.com/postcss/postcss) from 8.5.6 to 8.5.14.
    - [Release notes](https://github.com/postcss/postcss/releases)
    - [Changelog](https://github.com/postcss/postcss/blob/main/CHANGELOG.md)
    - [Commits](https://github.com/postcss/postcss/compare/8.5.6...8.5.14)
    ---
    updated-dependencies:
2026-05-19 Bump idna from 3.11 to 3.15 in /python/web
    Bumps [idna](https://github.com/kjd/idna) from 3.11 to 3.15.
    - [Release notes](https://github.com/kjd/idna/releases)
    - [Changelog](https://github.com/kjd/idna/blob/master/HISTORY.md)
    - [Commits](https://github.com/kjd/idna/compare/v3.11...v3.15)
    ---
    updated-dependencies:
2026-05-25 Bump SonarSource/sonarqube-scan-action in /.github/workflows
    Bumps [SonarSource/sonarqube-scan-action](https://github.com/sonarsource/sonarqube-scan-action) from 7.0.0 to 8.1.0.
    - [Release notes](https://github.com/sonarsource/sonarqube-scan-action/releases)
    - [Commits](https://github.com/sonarsource/sonarqube-scan-action/compare/a31c9398be7ace6bbfaf30c0bd5d415f843d45e9...7006c4492b2e0ee0f816d36501671557c97f5995)
    ---
    updated-dependencies:
    - dependency-name: SonarSource/sonarqube-scan-action
